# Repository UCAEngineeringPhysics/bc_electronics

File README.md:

# Electrical Engineering for BearCart

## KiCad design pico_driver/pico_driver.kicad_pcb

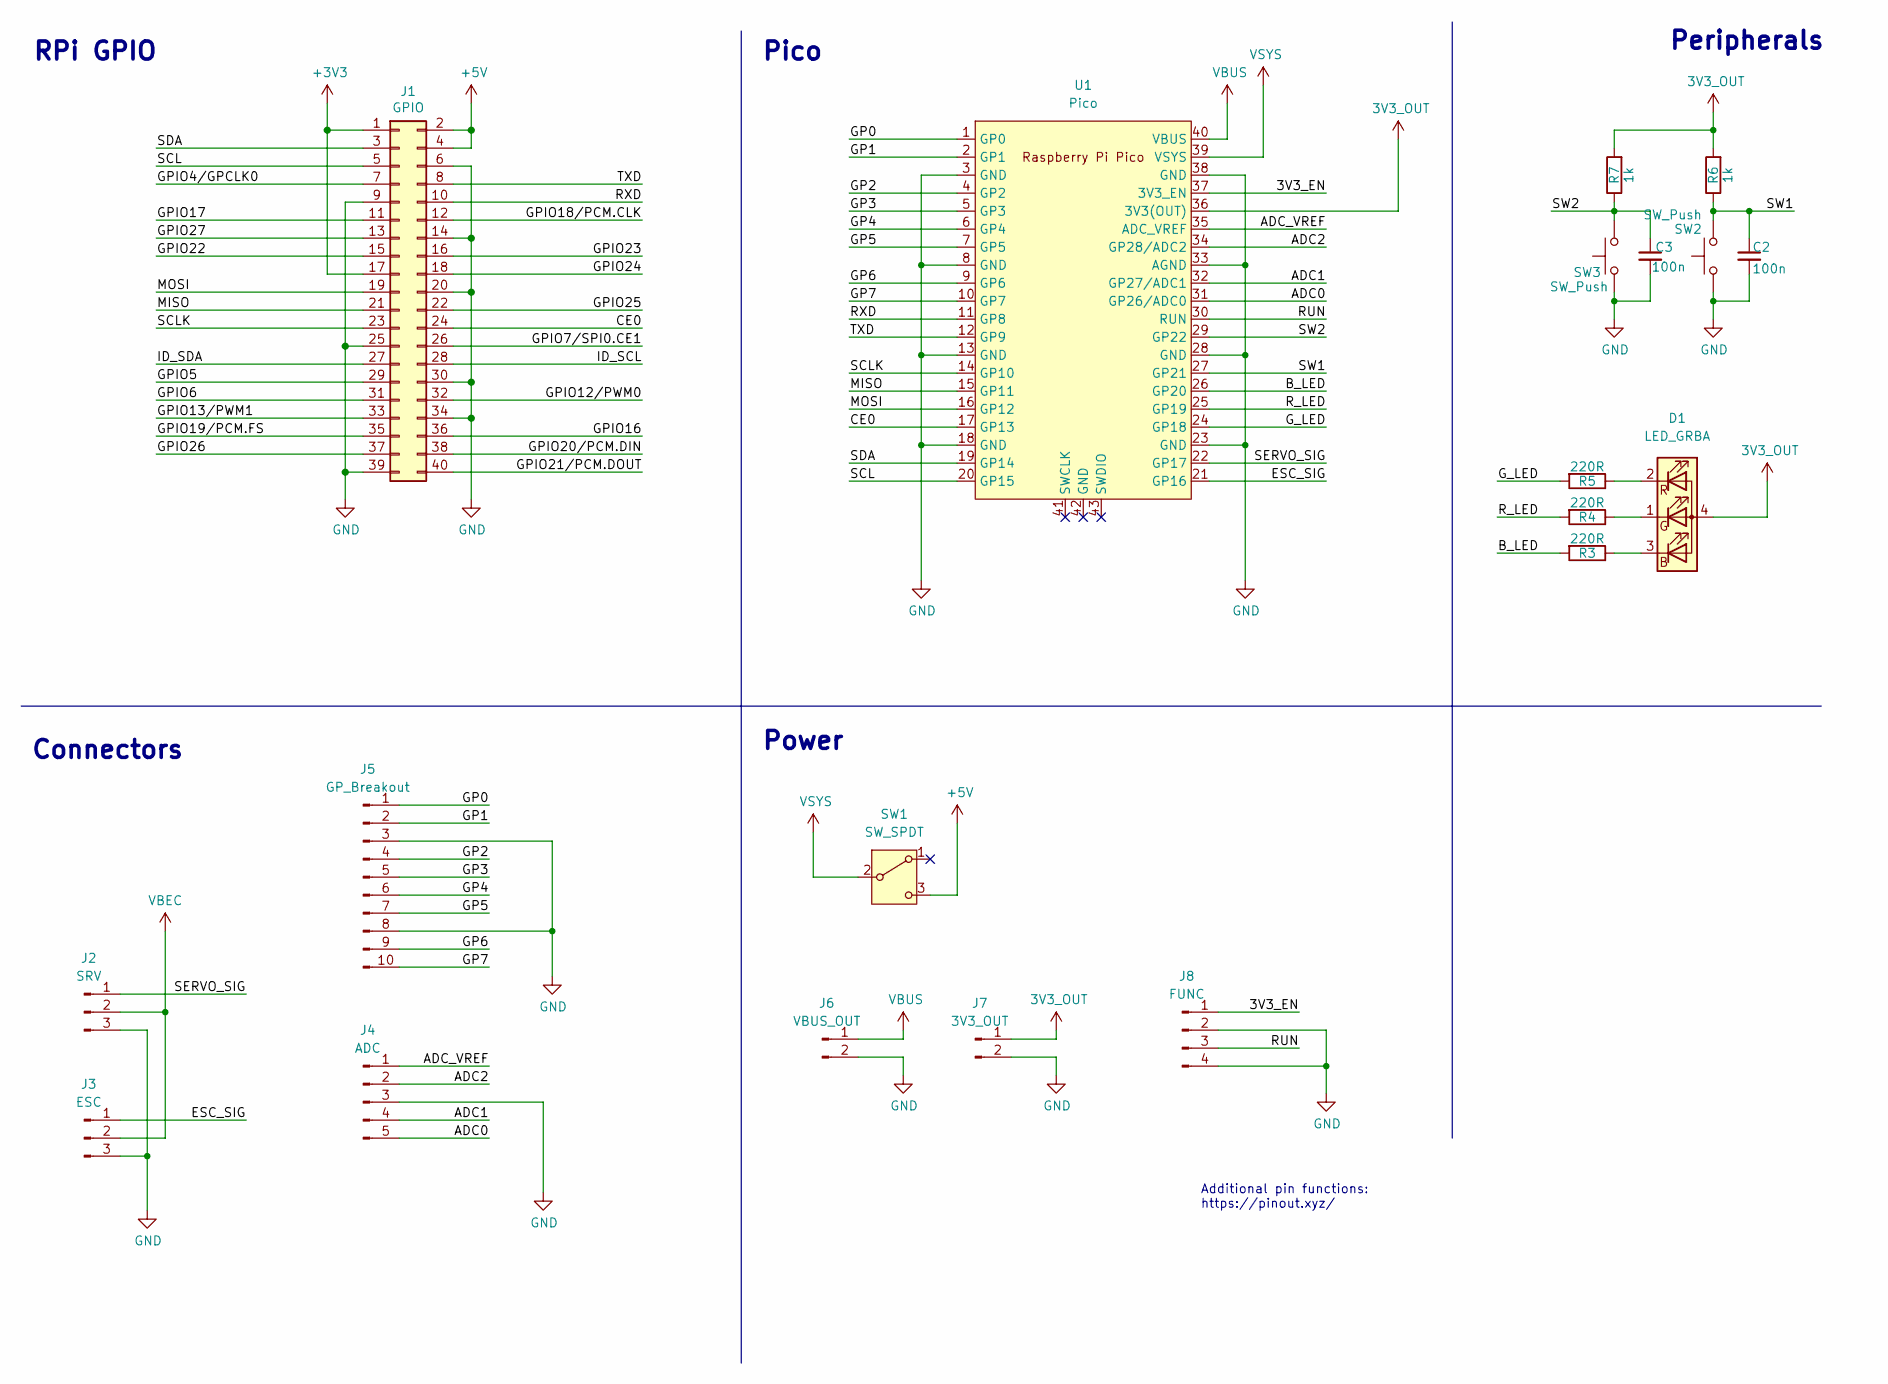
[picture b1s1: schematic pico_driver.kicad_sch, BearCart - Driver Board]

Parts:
C2, C3: 100n; C_0805_2012Metric_Pad1.18x1.45mm_HandSolder
D1: LED_GRBA; LED_RGB_1210
J1: GPIO; PinSocket_2x20_P2.54mm_Vertical
J2: SRV; PinHeader_1x03_P2.54mm_Horizontal
J3: ESC; PinHeader_1x03_P2.54mm_Vertical
J4: ADC; PinHeader_1x05_P2.54mm_Vertical
J5: GP_Breakout; PinHeader_1x10_P2.54mm_Vertical
J6: VBUS_OUT; PinHeader_1x02_P2.54mm_Vertical
J7: 3V3_OUT; PinHeader_1x02_P2.54mm_Vertical
J8: FUNC; PinHeader_1x04_P2.54mm_Vertical
R3, R4, R5: 220R; R_1206_3216Metric_Pad1.30x1.75mm_HandSolder
R6, R7: 1k; R_1206_3216Metric_Pad1.30x1.75mm_HandSolder
SW1: SW_SPDT; PinHeader_1x03_P2.54mm_Vertical
SW2, SW3: SW_Push; SW_PUSH_6mm_H5mm
U1: Pico; RaspberryPi_Pico_Common_THT

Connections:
3V3_OUT: D1.4 (A), J7.1, R6.2, R7.2, U1.36 (3V3(OUT))
+3V3: J1.1, J1.17
+5V: J1.2, J1.4, SW1.3 (C)
/3V3_EN: J8.1, U1.37 (3V3_EN)
/ADC0: J4.5, U1.31 (GP26/ADC0)
/ADC1: J4.4, U1.32 (GP27/ADC1)
/ADC2: J4.2, U1.34 (GP28/ADC2)
/ADC_VREF: J4.1, U1.35 (ADC_VREF)
/B_LED: R3.2, U1.26 (GP20)
/CE0: J1.24, U1.17 (GP13)
/ESC_SIG: J3.1, U1.21 (GP16)
/GP0: J5.1, U1.1 (GP0)
/GP1: J5.2, U1.2 (GP1)
/GP2: J5.4, U1.4 (GP2)
/GP3: J5.5, U1.5 (GP3)
/GP4: J5.6, U1.6 (GP4)
/GP5: J5.7, U1.7 (GP5)
/GP6: J5.9, U1.9 (GP6)
/GP7: J5.10, U1.10 (GP7)
/GPIO4/GPCLK0: J1.7
/GPIO5: J1.29
/GPIO6: J1.31
/GPIO7/SPI0.CE1: J1.26
/GPIO12/PWM0: J1.32
/GPIO13/PWM1: J1.33
/GPIO16: J1.36
/GPIO17: J1.11
/GPIO18/PCM.CLK: J1.12
/GPIO19/PCM.FS: J1.35
/GPIO20/PCM.DIN: J1.38
/GPIO21/PCM.DOUT: J1.40
/GPIO22: J1.15
/GPIO23: J1.16
/GPIO24: J1.18
/GPIO25: J1.22
/GPIO26: J1.37
/GPIO27: J1.13
/G_LED: R5.2, U1.24 (GP18)
/ID_SCL: J1.28
/ID_SDA: J1.27
/MISO: J1.21, U1.15 (GP11)
/MOSI: J1.19, U1.16 (GP12)
/RUN: J8.3, U1.30 (RUN)
/RXD: J1.10, U1.11 (GP8)
/R_LED: R4.2, U1.25 (GP19)
/SCL: J1.5, U1.20 (GP15)
/SCLK: J1.23, U1.14 (GP10)
/SDA: J1.3, U1.19 (GP14)
/SERVO_SIG: J2.1, U1.22 (GP17)
/SW1: C2.1, R6.1, SW2.2, U1.27 (GP21)
/SW2: C3.1, R7.1, SW3.2, U1.29 (GP22)
/TXD: J1.8, U1.12 (GP9)
GND: C2.2, C3.2, J1.6, J1.9, J1.14, J1.20, J1.25, J1.30, J1.34, J1.39, J2.3, J3.3, J4.3, J5.3, J5.8, J6.2, J7.2, J8.2, J8.4, SW2.1, SW3.1, U1.3 (GND), U1.8 (GND), U1.13 (GND), U1.18 (GND), U1.23 (GND), U1.28 (GND), U1.33 (AGND), U1.38 (GND)
unnamed: D1.3 (BK), R3.1
unnamed: D1.1 (GK), R4.1
unnamed: D1.2 (RK), R5.1
VBEC: J2.2, J3.2
VBUS: J6.1, U1.40 (VBUS)
VSYS: SW1.2 (B), U1.39 (VSYS)

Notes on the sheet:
Additional pin functions: https://pinout.xyz/
Power
RPi GPIO
Peripherals
Pico
Connectors

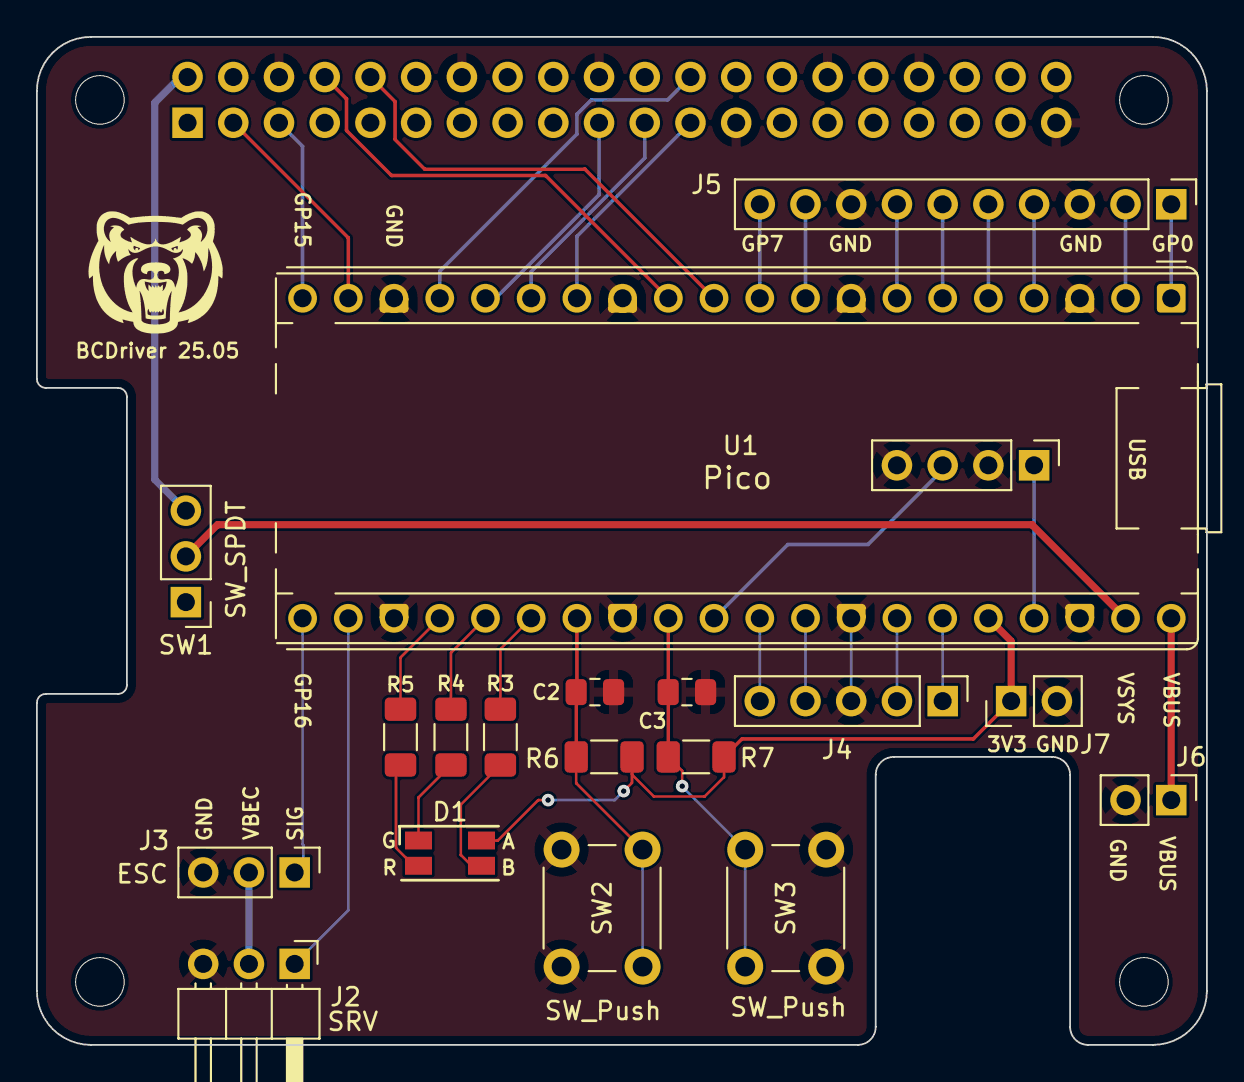
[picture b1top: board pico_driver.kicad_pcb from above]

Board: 4 copper layers, 65.0 x 56.0 mm, 24 parts (1 on the bottom side), 39 nets.

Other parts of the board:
MH1, MH2, MH3, MH4: MountingHole_2.7mm_M2.5

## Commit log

2025-04-16 init pico carrier board stack on pi
2025-04-16 remove old project
2025-04-16 init kicad 9 project
2025-04-16 update schematic
2025-04-16 update pico symbol
2025-04-17 create bear logo
2025-04-17 add eeprom lib
2025-04-17 update design
2025-04-17 add gerbers
2025-04-24 update design
    1. paralleled capacitor to debounce buttons
    2. rewired
    3. generated gerbers
2025-04-24 save project
2025-04-25 export schematic pdf
2025-04-25 update schematic
    removed eeprom
2025-04-25 update pico footprint
2025-04-25 update schematic
    - updated wiring
    - added more breakout connector pins
2025-04-25 update pcb layout
2025-04-25 wire up pcb
2025-04-25 minor update pcb
    added a few text labels
2025-04-25 generate new gerbers
2025-04-25 update schematic pdf
2025-05-15 remove old and unused items
2025-05-15 update schemetic and pcb
    Pin header for sw1
2025-05-15 generate gerbers for JLC
2025-05-15 generate gerbers for PCBWAY
2025-05-17 update esc and servo pin layout
2025-05-17 update LED footprint
2025-05-17 update rgb led footprint
2025-05-18 update rgb led footprint and layout
2025-05-18 update schematic info
2025-05-18 export updated schematic
2025-05-24 generate updated gerbers
2025-05-24 zip gerbers for jlcpcb
2025-05-24 remove old gerbers
